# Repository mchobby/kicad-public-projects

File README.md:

# kicad-public-projects
Kicad's Public Project from shop.MCHobby.be

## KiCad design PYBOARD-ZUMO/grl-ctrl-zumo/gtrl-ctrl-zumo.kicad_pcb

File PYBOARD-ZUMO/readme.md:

# Pyboard Zumo

The subfolder folder [grl-pyboard-zumo](grl-pyboard-zumo) is an adaptater board designed to control a __Zumo Robot for Arduino__ from a MicroPython Pyboard.

This folder contains gerber file and kicad design files. Be curious, there is also an extension board.

See also:

* [micropython-zumo-robot Github repository](https://github.com/mchobby/micropython-zumo-robot) for MicroPython source code.
* Product: [Pyboard to Zumo adapter](https://shop.mchobby.be/fr/micropython/2040-adaptateur-pyboard-pour-zumo-robot-3232100020405.html) (__deprecated__)
* [Pico to Zumo Robot adapter - Pico included - FR EBook included](https://shop.mchobby.be/en/micropython/2430-pico-to-zumo-robot-adapter-3232100024304.html)

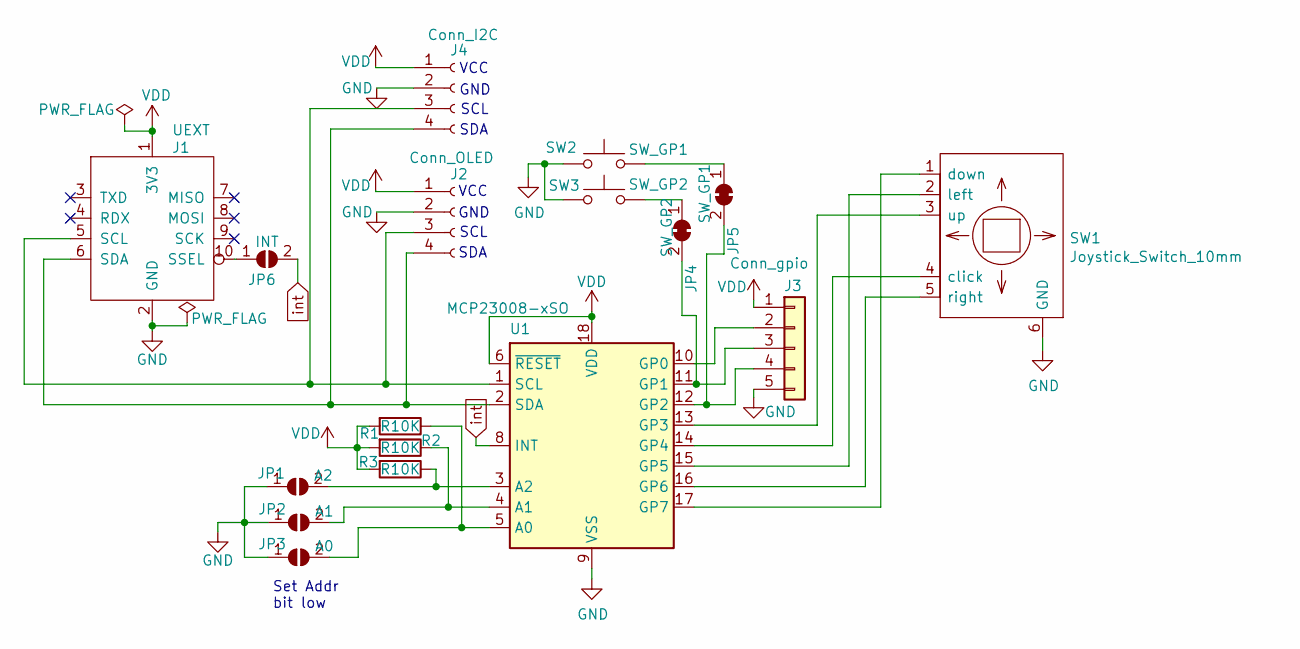
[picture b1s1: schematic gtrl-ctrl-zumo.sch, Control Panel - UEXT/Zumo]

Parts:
J1: UEXT; IDC-Header_2x05_P2.54mm_Vertical
J2: Conn_OLED; PinHeader_1x04_P2.54mm_Vertical
J3: Conn_gpio; PinHeader_1x05_P2.54mm_Vertical
J4: Conn_I2C; PinHeader_1x04_P2.54mm_Vertical
JP1: A2; SolderJumper-2_P1.3mm_Open_Pad1.0x1.5mm
JP2: A1; SolderJumper-2_P1.3mm_Open_Pad1.0x1.5mm
JP3: A0; SolderJumper-2_P1.3mm_Open_Pad1.0x1.5mm
JP4: SW_GP2; SolderJumper-2_P1.3mm_Bridged_Pad1.0x1.5mm
JP5: SW_GP1; SolderJumper-2_P1.3mm_Bridged_Pad1.0x1.5mm
JP6: INT; SolderJumper-2_P1.3mm_Open_Pad1.0x1.5mm
R1, R2, R3: R10K; R_1206_3216Metric_Pad1.30x1.75mm_HandSolder
SW1: Joystick_Switch_10mm
SW2: SW_GP1; SW_Push_TL3305G_NO_4.5x4.5mm_H4.5mm
SW3: SW_GP2; SW_Push_TL3305G_NO_4.5x4.5mm_H4.5mm
U1: MCP23008-xSO; SOIC-18W_7.5x11.6mm_P1.27mm

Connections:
GND: J1.2 (GND), J2.2, J3.5, J4.2, JP1.1 (A), JP2.1 (A), JP3.1 (A), SW1.6 (GND), SW2.1, SW3.1, U1.9 (VSS)
unnamed: J1.5 (SCL), J2.3, J4.3, U1.1 (SCL)
unnamed: J1.6 (SDA), J2.4, J4.4, U1.2 (SDA)
unnamed: J1.10 (SSEL), JP6.1 (A)
unnamed: J3.2, U1.10 (GP0)
unnamed: J3.3, JP4.2 (B), U1.11 (GP1)
unnamed: J3.4, JP5.2 (B), U1.12 (GP2)
unnamed: JP1.2 (B), R3.1, U1.3 (A2)
unnamed: JP2.2 (B), R2.1, U1.4 (A1)
unnamed: JP3.2 (B), R1.1, U1.5 (A0)
unnamed: JP4.1 (A), SW3.2
unnamed: JP5.1 (A), SW2.2
unnamed: SW1.1 (down), U1.17 (GP7)
unnamed: SW1.2 (left), U1.15 (GP5)
unnamed: SW1.3 (up), U1.13 (GP3)
unnamed: SW1.4 (click), U1.14 (GP4)
unnamed: SW1.5 (right), U1.16 (GP6)
VDD: J1.1 (3V3), J2.1, J3.1, J4.1, R1.2, R2.2, R3.2, U1.6 (~RESET), U1.18 (VDD)
int: JP6.2 (B), U1.8 (INT)

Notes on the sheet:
VCC
GND
SCL
SDA
Set Addr bit low

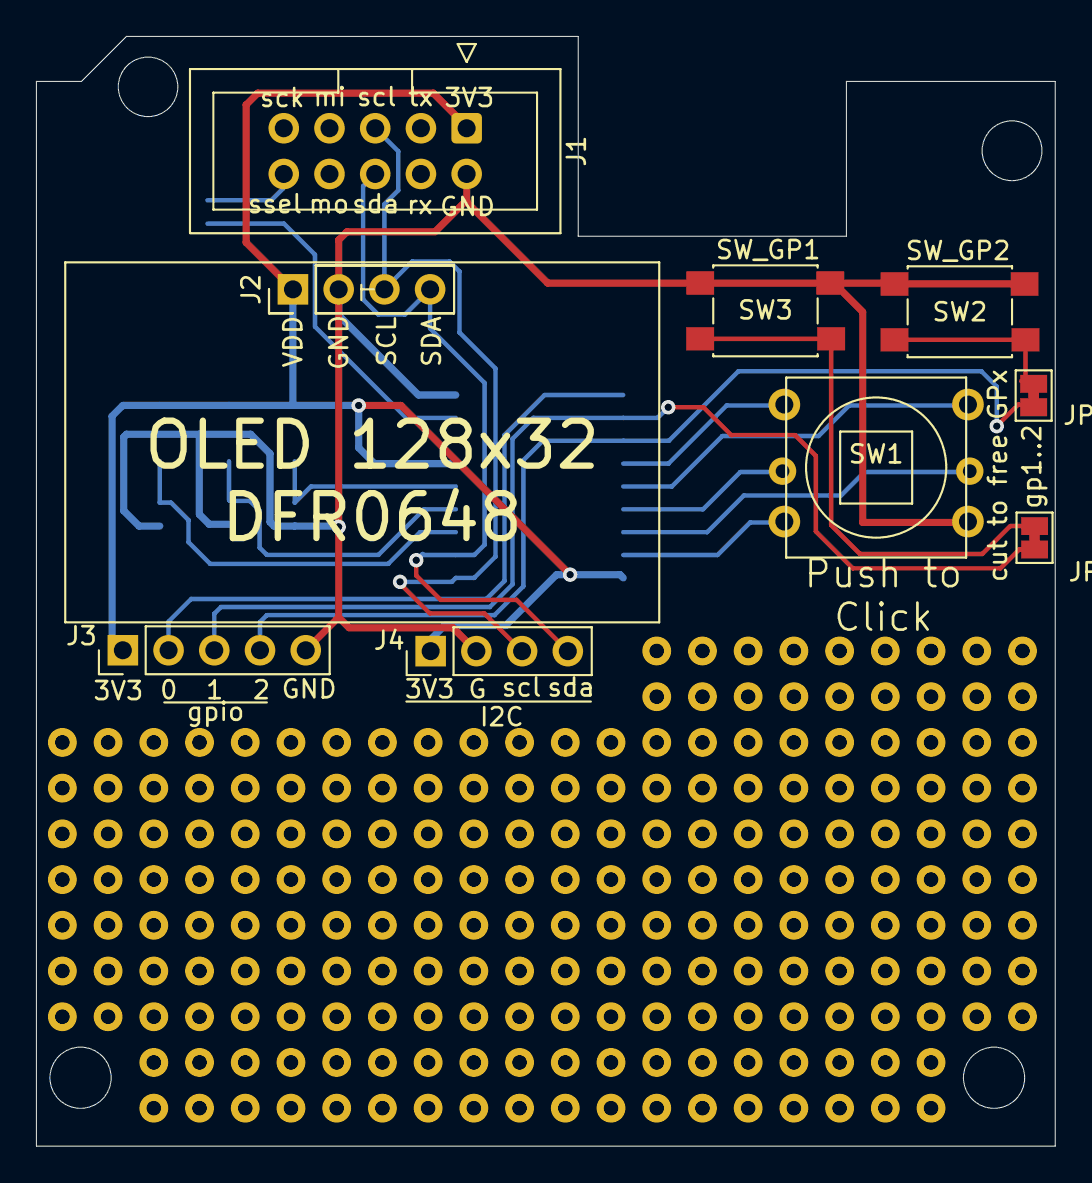
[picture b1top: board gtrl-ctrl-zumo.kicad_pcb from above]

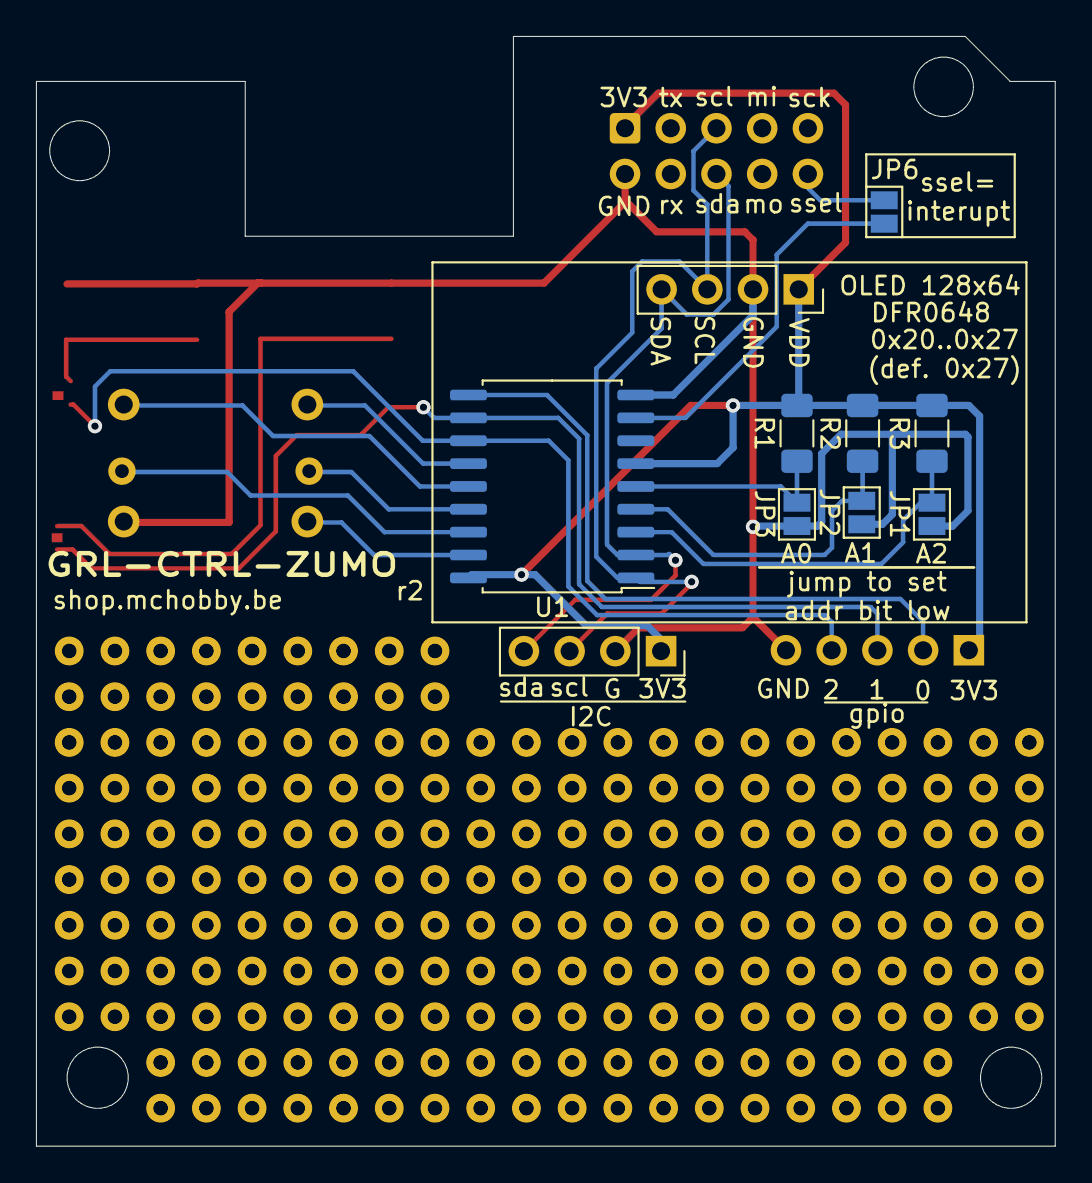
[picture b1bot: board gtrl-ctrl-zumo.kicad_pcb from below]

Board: 2 copper layers, 56.6 x 61.7 mm, 17 parts (8 on the bottom side), 19 nets.

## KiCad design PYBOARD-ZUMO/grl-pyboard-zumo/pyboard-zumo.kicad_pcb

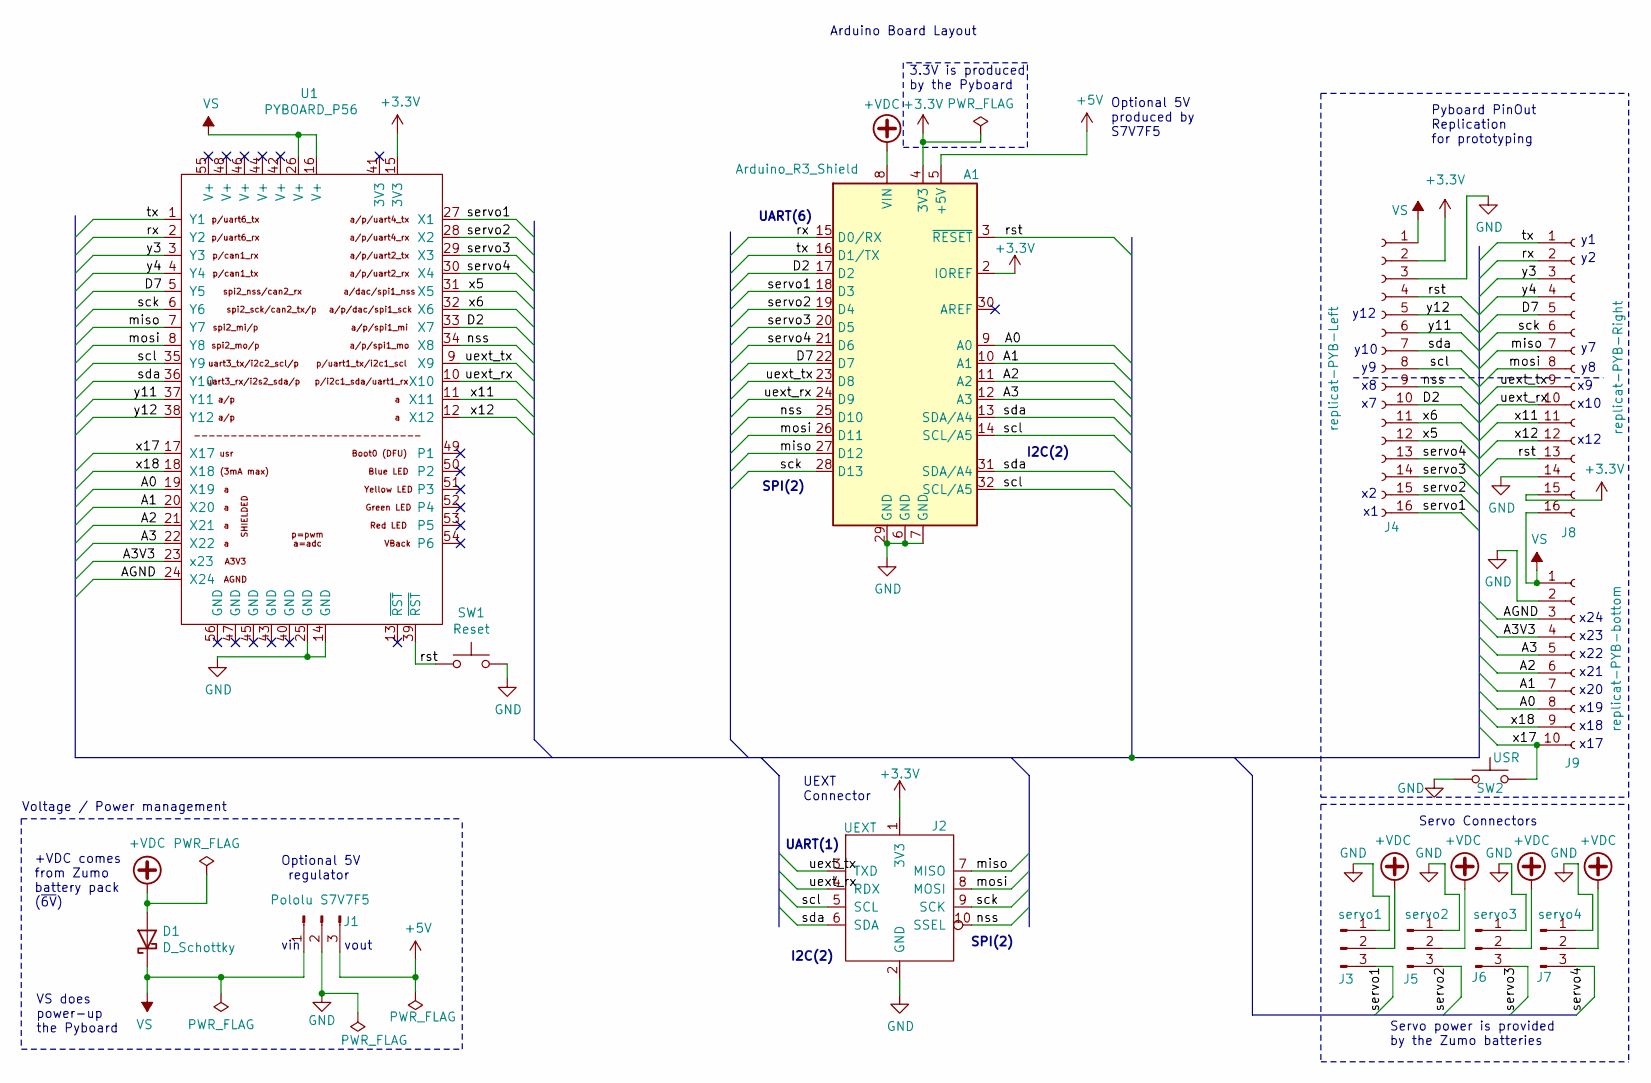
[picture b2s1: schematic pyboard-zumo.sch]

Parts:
A1: Arduino_R3_Shield; Arduino_UNO_R3
D1: D_Schottky; D_5W_P12.70mm_Horizontal
J1: Pololu S7V7F5; PinHeader_1x03_P2.54mm_Vertical
J2: UEXT; IDC-Header_2x05_P2.54mm_Vertical
J3: servo1; PinHeader_1x03_P2.54mm_Vertical
J4: replicat-PYB-Left; PinHeader_1x16_P2.54mm_Vertical
J5: servo2; PinHeader_1x03_P2.54mm_Vertical
J6: servo3; PinHeader_1x03_P2.54mm_Vertical
J7: servo4; PinHeader_1x03_P2.54mm_Vertical
J8: replicat-PYB-Right; PinHeader_1x16_P2.54mm_Vertical
J9: replicat-PYB-bottom; PinHeader_1x10_P2.54mm_Vertical
SW1: Reset; SW_PUSH_6mm
SW2: USR; SW_PUSH_6mm
U1: PYBOARD_P56; Pyboard_L42mm_W35mm_P2.54mm

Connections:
+3V3: A1.2 (IOREF), A1.4 (3V3), J2.1 (3V3), J4.2, J8.15, U1.15 (3V3)
+5V: A1.5 (+5V), J1.3
+VDC: A1.8 (VIN), D1.2 (A), J3.2, J5.2, J6.2, J7.2
/A0: A1.9 (A0), J9.8, U1.19 (X19)
/A1: A1.10 (A1), J9.7, U1.20 (X20)
/A2: A1.11 (A2), J9.6, U1.21 (X21)
/A3: A1.12 (A3), J9.5, U1.22 (X22)
/A3V3: J9.4, U1.23 (x23)
/AGND: J9.3, U1.24 (X24)
/D2: A1.17 (D2), J4.10, U1.33 (X7)
/D7: A1.22 (D7), J8.5, U1.5 (Y5)
/miso: A1.27 (D12), J2.7 (MISO), J8.7, U1.7 (Y7)
/mosi: A1.26 (D11), J2.8 (MOSI), J8.8, U1.8 (Y8)
/nss: A1.25 (D10), J2.10 (SSEL), J4.9, U1.34 (X8)
/rst: A1.3 (~RESET), J4.4, J8.13, SW1.1, U1.39 (~RST)
/rx: A1.15 (D0/RX), J8.2, U1.2 (Y2)
/sck: A1.28 (D13), J2.9 (SCK), J8.6, U1.6 (Y6)
/scl: A1.14 (SCL/A5), A1.32 (SCL/A5), J2.5 (SCL), J4.8, U1.35 (Y9)
/sda: A1.13 (SDA/A4), A1.31 (SDA/A4), J2.6 (SDA), J4.7, U1.36 (Y10)
/servo1: A1.18 (D3), J3.3, J4.16, U1.27 (X1)
/servo2: A1.19 (D4), J4.15, J5.3, U1.28 (X2)
/servo3: A1.20 (D5), J4.14, J6.3, U1.29 (X3)
/servo4: A1.21 (D6), J4.13, J7.3, U1.30 (X4)
/tx: A1.16 (D1/TX), J8.1, U1.1 (Y1)
/uext_rx: A1.24 (D9), J2.4 (RDX), J8.10, U1.10 (X10)
/uext_tx: A1.23 (D8), J2.3 (TXD), J8.9, U1.9 (X9)
/x5: J4.12, U1.31 (X5)
/x6: J4.11, U1.32 (X6)
/x11: J8.11, U1.11 (X11)
/x12: J8.12, U1.12 (X12)
/x17: J9.10, SW2.2, U1.17 (X17)
/x18: J9.9, U1.18 (X18)
/y3: J8.3, U1.3 (Y3)
/y4: J8.4, U1.4 (Y4)
/y11: J4.6, U1.37 (Y11)
/y12: J4.5, U1.38 (Y12)
GND: A1.6 (GND), A1.7 (GND), A1.29 (GND), J1.2, J2.2 (GND), J3.1, J4.3, J5.1, J6.1, J7.1, J8.14, J9.2, SW1.2, SW2.1, U1.14 (GND), U1.25 (GND)
VS: D1.1 (K), J1.1, J4.1, J8.16, J9.1, U1.16 (V+), U1.26 (V+)

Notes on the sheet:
Arduino Board Layout
Voltage / Power management
+VDC comes from Zumo battery pack (~6V)
VS does power-up the Pyboard
3.3V is produced by the Pyboard
Optional 5V regulator
vin
vout
Optional 5V produced by S7V7F5
I2C(2)
SPI(2)
UART(6)
UART(1)
Pyboard PinOut Replication for prototyping
UEXT Connector
y10
y12
x10
x12
x24
x20
x22
x21
x19
x23
x18
x17
Servo Connectors
Servo power is provided by the Zumo batteries

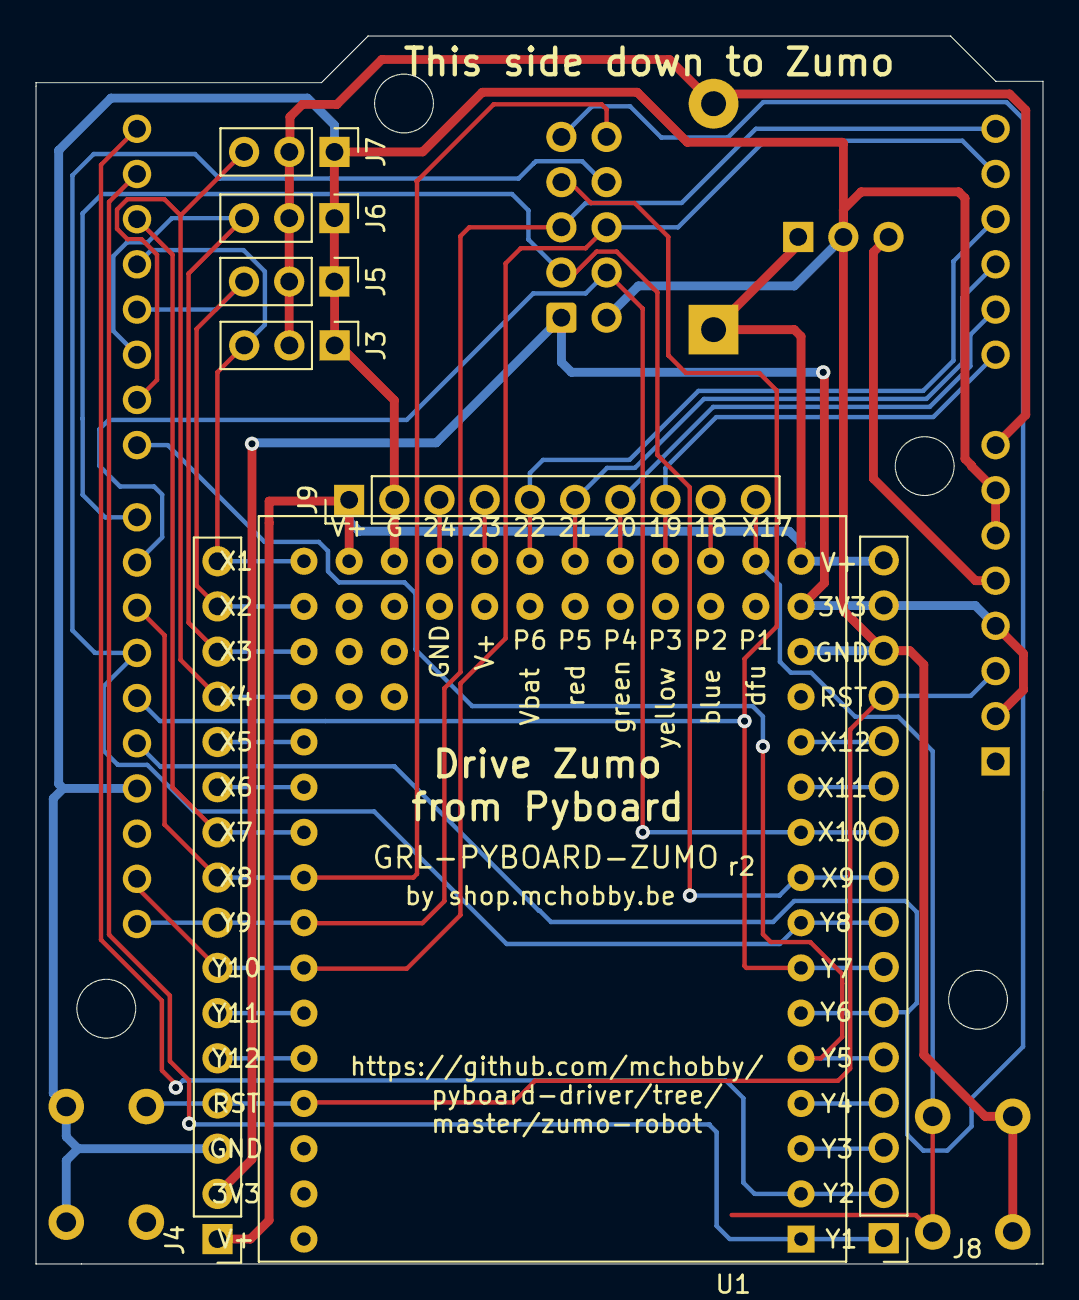
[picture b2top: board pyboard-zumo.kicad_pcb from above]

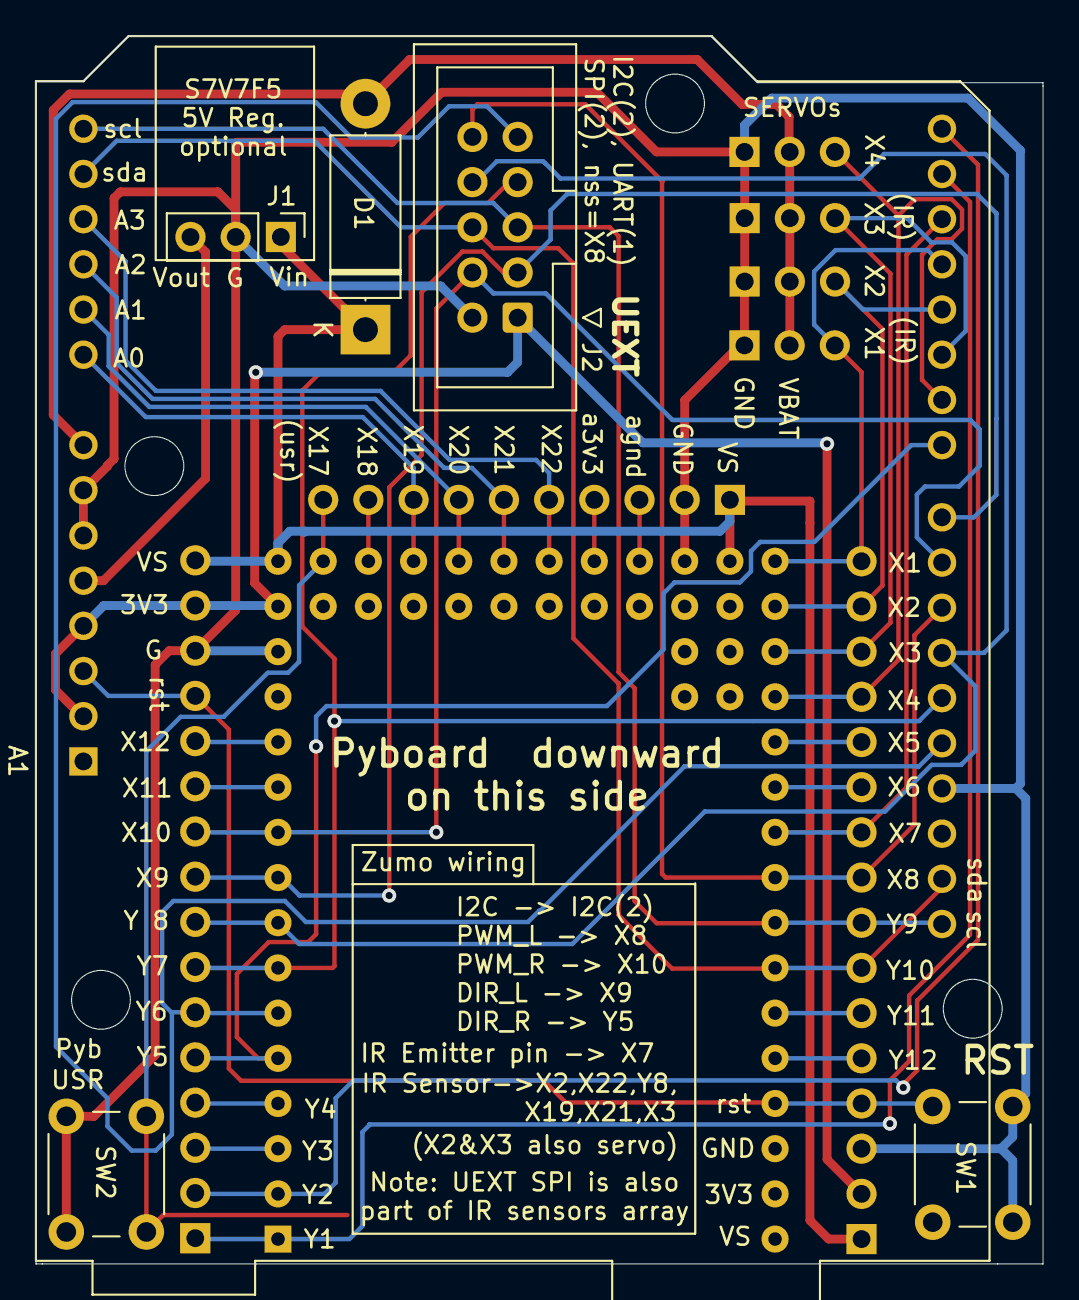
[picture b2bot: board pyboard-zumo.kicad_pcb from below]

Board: 2 copper layers, 56.6 x 69.0 mm, 14 parts (6 on the bottom side), 38 nets.

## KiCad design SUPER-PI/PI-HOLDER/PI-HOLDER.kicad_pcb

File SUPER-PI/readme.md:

# Super-Pi - Cartes du projet

Super-Pi est un Super Calculateur DIY developpés à partir de Raspberry-Pis.

Ce dépôt contient les cartes développées spécialement pour le projet Super-Pi.

Voir le [Wiki du projet Super-Pi pour les détails](https://wiki.mchobby.be/index.php?title=SuperPi-Accueil)

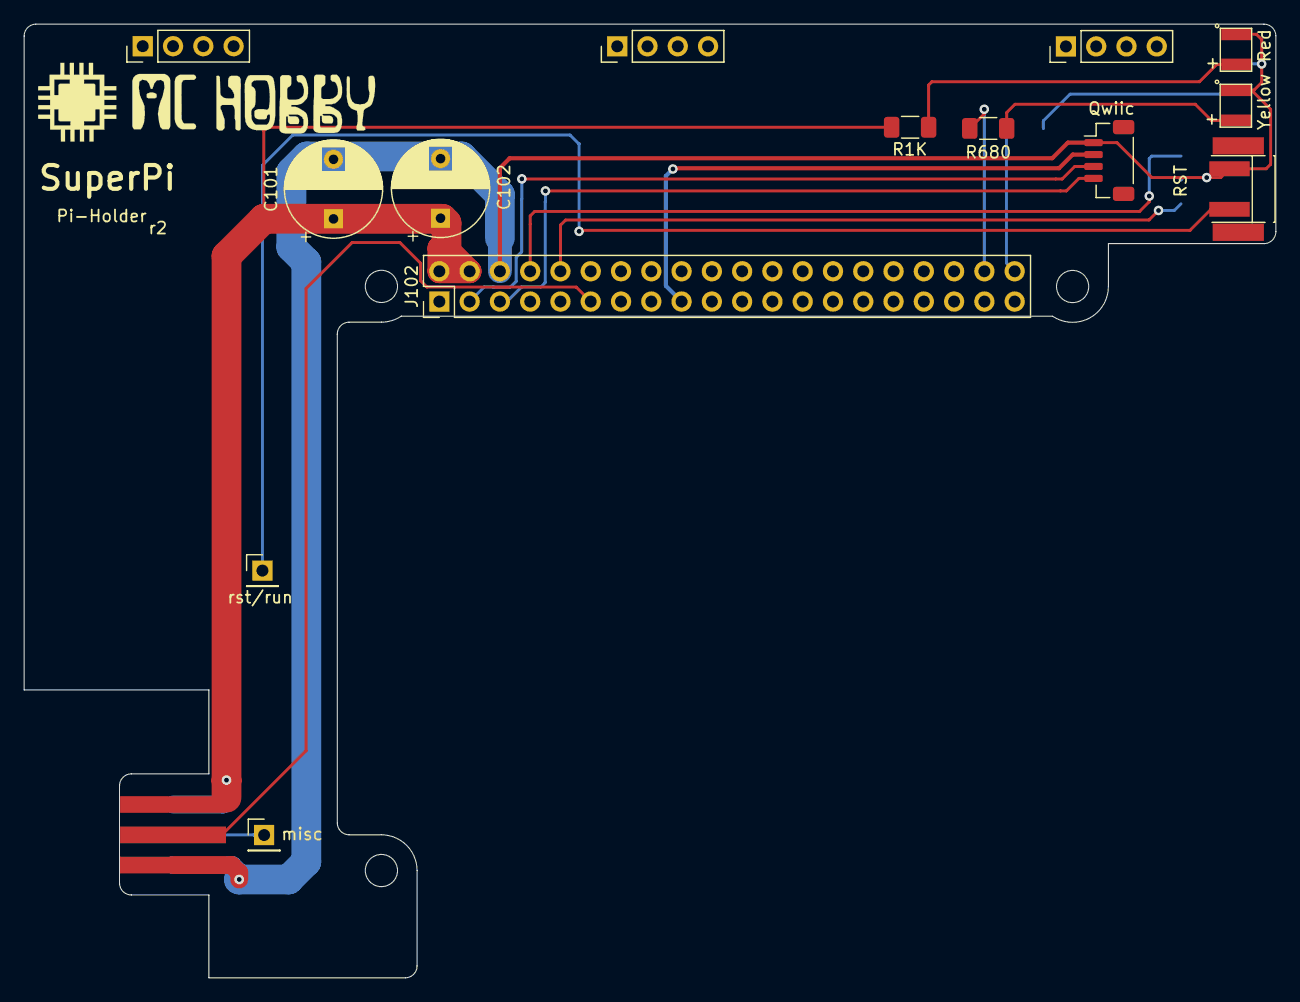
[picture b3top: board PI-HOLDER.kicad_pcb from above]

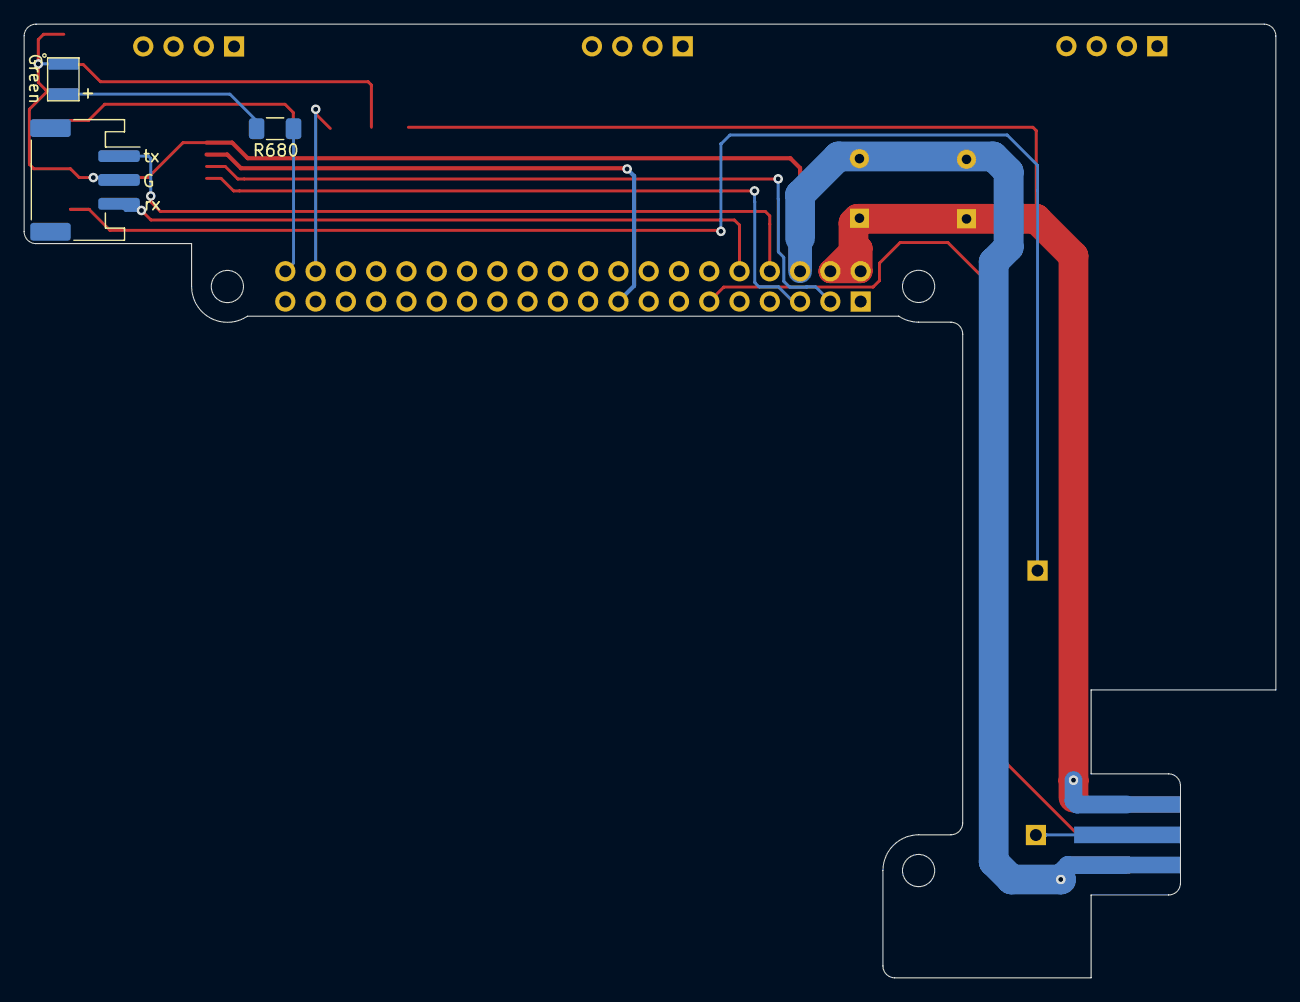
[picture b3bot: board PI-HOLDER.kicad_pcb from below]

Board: 2 copper layers, 105.0 x 80.0 mm, 15 parts (3 on the bottom side), 15 nets.

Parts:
C101, C102: CP; CP_Radial_D8.0mm_P5.00mm
D101: LED Yellow; PadHeader_1x02_P2.54mm_SMD
D102: LED Green; PadHeader_1x02_P2.54mm_SMD
D103: LED Red; PadHeader_1x02_P2.54mm_SMD
J101: Conn_RackPwr; STD_EDGE_II_6pos_2x03_P2.54_Edge
J102: Conn_GPIO; PinHeader_2x20_P2.54mm_Vertical
J103: Conn_RST; PinHeader_1x01_P2.54mm_Vertical
J104: Conn_Qwiic; JST_SH_BM04B-SRSS-TB_1x04-1MP_P1.00mm_Vertical
J105: Conn_UART; JST_PH_S3B-PH-SM4-TB_1x03-1MP_P2.00mm_Horizontal
J106: Conn_misc; PinHeader_1x01_P2.54mm_Vertical
R101, R102: R680; R_1206_3216Metric_Pad1.30x1.75mm_HandSolder
R103: R1K; R_1206_3216Metric_Pad1.30x1.75mm_HandSolder
SW101: SW_RST; SW_Push_TL1571407-90_NO_8.7x5.5mm_H7mm

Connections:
+3V3: J102.17, J104.2
+5V: C101.1, C102.1, J101.1, J101.6, J102.2, J102.4, R103.2
/gp20: J102.38, R101.2
/gp21: J102.40, R102.2
/misc: J101.5, J106.1
/panic: J101.2, J102.11
/rxd: J102.10, J105.3
/scl: J102.5, J104.4
/sda: J102.3, J104.3
/txd: J102.8, J105.1
GND: C101.2, C102.2, D101.1, D102.1, D103.1, J101.3, J101.4, J102.6, J104.1, J105.2, SW101.2
unnamed: D101.2, R101.1
unnamed: D102.2, R102.1
unnamed: D103.2, R103.1
unnamed: J103.1, SW101.1

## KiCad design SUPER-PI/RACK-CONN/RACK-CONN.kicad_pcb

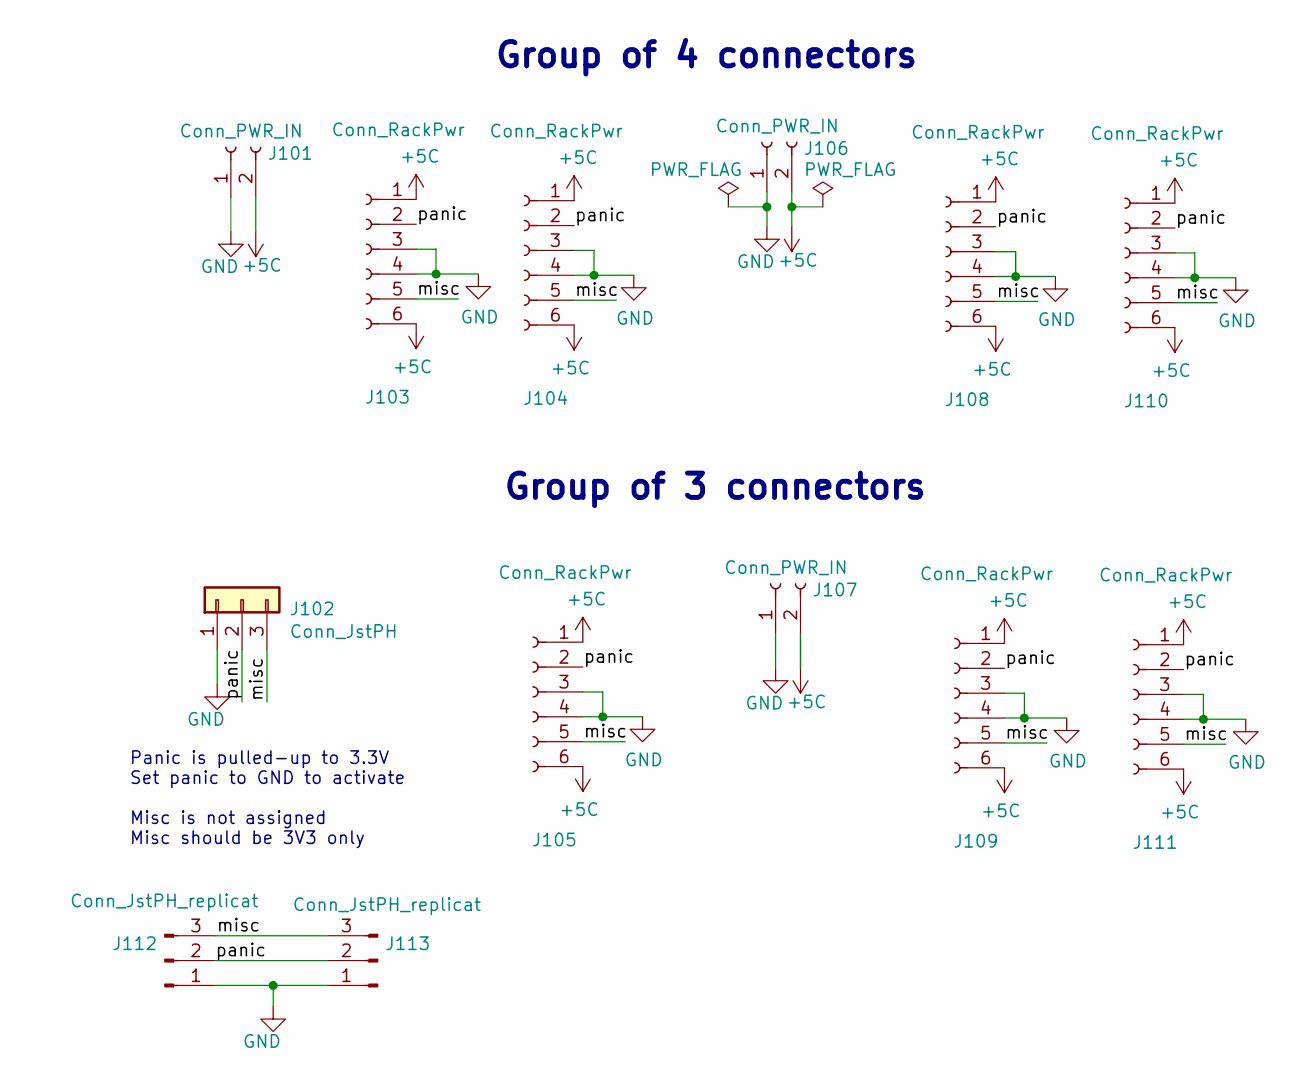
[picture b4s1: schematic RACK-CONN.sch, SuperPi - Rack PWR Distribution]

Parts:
J101, J106, J107: Conn_PWR_IN; PinHeader_1x02_P5.08mm_Vertical
J102: Conn_JstPH; JST_PH_S3B-PH-SM4-TB_1x03-1MP_P2.00mm_Horizontal
J103, J104, J105, J108, J109, J110, J111: Conn_RackPwr; STD_EDGE_II_6pos_Card_Edge_Conn
J112, J113: Conn_JstPH_replicat; PadHeader_1x03_P2.54mm_SMD

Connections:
+5C: J101.2, J103.1, J103.6, J104.1, J104.6, J105.1, J105.6, J106.2, J107.2, J108.1, J108.6, J109.1, J109.6, J110.1, J110.6, J111.1, J111.6
/misc: J102.3, J103.5, J104.5, J105.5, J108.5, J109.5, J110.5, J111.5, J112.3, J113.3
/panic: J102.2, J103.2, J104.2, J105.2, J108.2, J109.2, J110.2, J111.2, J112.2, J113.2
GND: J101.1, J102.1, J103.3, J103.4, J104.3, J104.4, J105.3, J105.4, J106.1, J107.1, J108.3, J108.4, J109.3, J109.4, J110.3, J110.4, J111.3, J111.4, J112.1, J113.1

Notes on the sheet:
Group of 4 connectors
Group of 3 connectors
Panic is pulled-up to 3.3V Set panic to GND to activate Misc is not assigned Misc should be 3V3 only

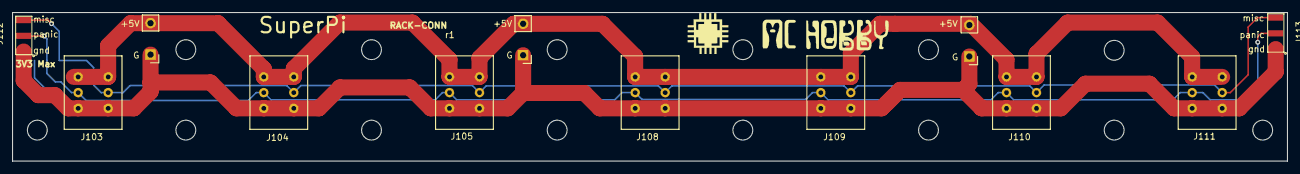
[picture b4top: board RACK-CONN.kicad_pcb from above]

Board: 2 copper layers, 206.0 x 24.0 mm, 13 parts (1 on the bottom side), 4 nets.
